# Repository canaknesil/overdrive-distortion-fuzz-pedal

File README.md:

# overdrive-distortion-fuzz-pedal
Overdrive, distortion, and fuzz with a single pedal

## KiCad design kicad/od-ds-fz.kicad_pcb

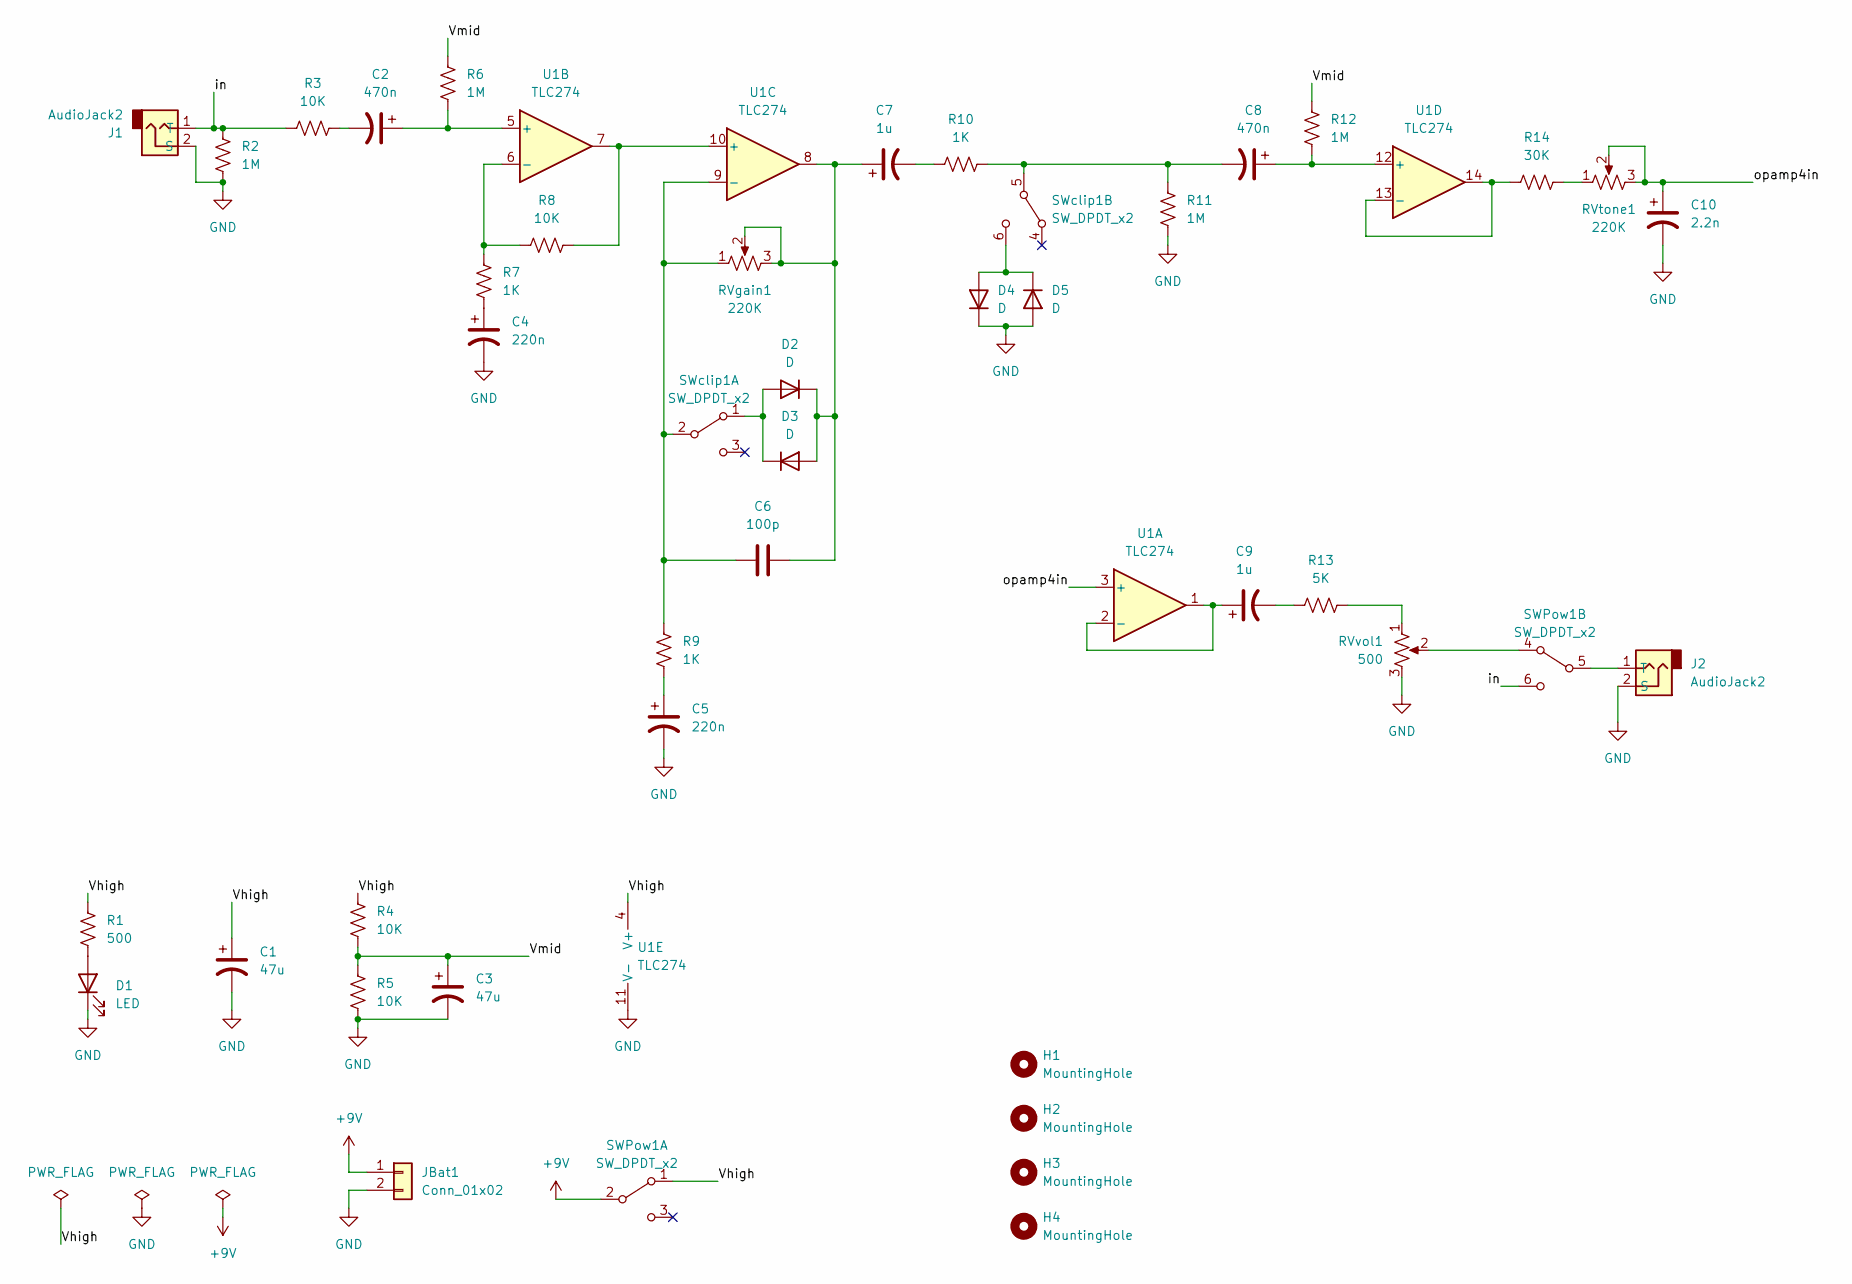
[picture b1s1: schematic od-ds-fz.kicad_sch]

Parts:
C1, C3: 47u; CP_Radial_D7.5mm_P2.50mm
C2, C8: 470n; CP_Radial_D7.5mm_P2.50mm
C4, C5: 220n; CP_Radial_D7.5mm_P2.50mm
C6: 100p; C_Disc_D5.1mm_W3.2mm_P5.00mm
C7, C9: 1u; CP_Radial_D7.5mm_P2.50mm
C10: 2.2n; C_Disc_D5.1mm_W3.2mm_P5.00mm
D1: LED; SolderWire-0.5sqmm_1x02_P4.6mm_D0.9mm_OD2.1mm
D2, D3, D4, D5: D; D_DO-15_P15.24mm_Horizontal
H1, H2, H3, H4: MountingHole; MountingHole_3.2mm_M3
J1, J2: AudioJack2; SolderWire-0.5sqmm_1x02_P4.6mm_D0.9mm_OD2.1mm
JBat1: Conn_01x02; SolderWire-0.5sqmm_1x02_P4.6mm_D0.9mm_OD2.1mm
R1: 500; R_Axial_DIN0207_L6.3mm_D2.5mm_P10.16mm_Horizontal
R2, R6, R11, R12: 1M; R_Axial_DIN0207_L6.3mm_D2.5mm_P10.16mm_Horizontal
R3, R4, R5, R8: 10K; R_Axial_DIN0207_L6.3mm_D2.5mm_P10.16mm_Horizontal
R7, R9, R10: 1K; R_Axial_DIN0207_L6.3mm_D2.5mm_P10.16mm_Horizontal
R13: 5K; R_Axial_DIN0207_L6.3mm_D2.5mm_P10.16mm_Horizontal
R14: 30K; R_Axial_DIN0207_L6.3mm_D2.5mm_P10.16mm_Horizontal
RVgain1: 220K; SolderWire-0.5sqmm_1x03_P4.6mm_D0.9mm_OD2.1mm
RVtone1: 220K; SolderWire-0.5sqmm_1x03_P4.6mm_D0.9mm_OD2.1mm
RVvol1: 500; SolderWire-0.5sqmm_1x03_P4.6mm_D0.9mm_OD2.1mm
SWPow1: SW_DPDT_x2; SolderWire-0.5sqmm_1x06_P4.6mm_D0.9mm_OD2.1mm
SWclip1: SW_DPDT_x2; SolderWire-0.5sqmm_1x06_P4.6mm_D0.9mm_OD2.1mm
U1: TLC274; DIP-14_W7.62mm

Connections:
+9V: JBat1.1, SWPow1.2 (B)
/Vhigh: C1.1, R1.1, R4.1, SWPow1.1 (A), U1.4 (V+)
/Vmid: C3.1, R4.2, R5.1, R6.1, R12.1
/in: J1.1 (T), R2.1, R3.1, SWPow1.6 (C)
/opamp4in: C10.1, RVtone1.2, RVtone1.3, U1.3 (+)
GND: C1.2, C3.2, C4.2, C5.2, C10.2, D1.1 (K), D4.1 (K), D5.2 (A), J1.2 (S), J2.2 (S), JBat1.2, R2.2, R5.2, R11.2, RVvol1.3, U1.11 (V-)
unnamed: C2.1, R6.2, U1.5 (+)
unnamed: C2.2, R3.2
unnamed: C4.1, R7.2
unnamed: C5.1, R9.2
unnamed: C6.1, R9.1, RVgain1.1, SWclip1.2 (B), U1.9 (-)
unnamed: C6.2, C7.1, D2.1 (K), D3.2 (A), RVgain1.2, RVgain1.3, U1.8
unnamed: C7.2, R10.1
unnamed: C8.1, R12.2, U1.12 (+)
unnamed: C8.2, R10.2, R11.1, SWclip1.5 (B)
unnamed: C9.1, U1.1, U1.2 (-)
unnamed: C9.2, R13.1
unnamed: D1.2 (A), R1.2
unnamed: D2.2 (A), D3.1 (K), SWclip1.1 (A)
unnamed: D4.2 (A), D5.1 (K), SWclip1.6 (C)
unnamed: R7.1, R8.1, U1.6 (-)
unnamed: R8.2, U1.7, U1.10 (+)
unnamed: R13.2, RVvol1.1
unnamed: R14.1, U1.13 (-), U1.14
unnamed: R14.2, RVtone1.1
unnamed: RVvol1.2, SWPow1.4 (A)
unnamed: J2.1 (T), SWPow1.5 (B)

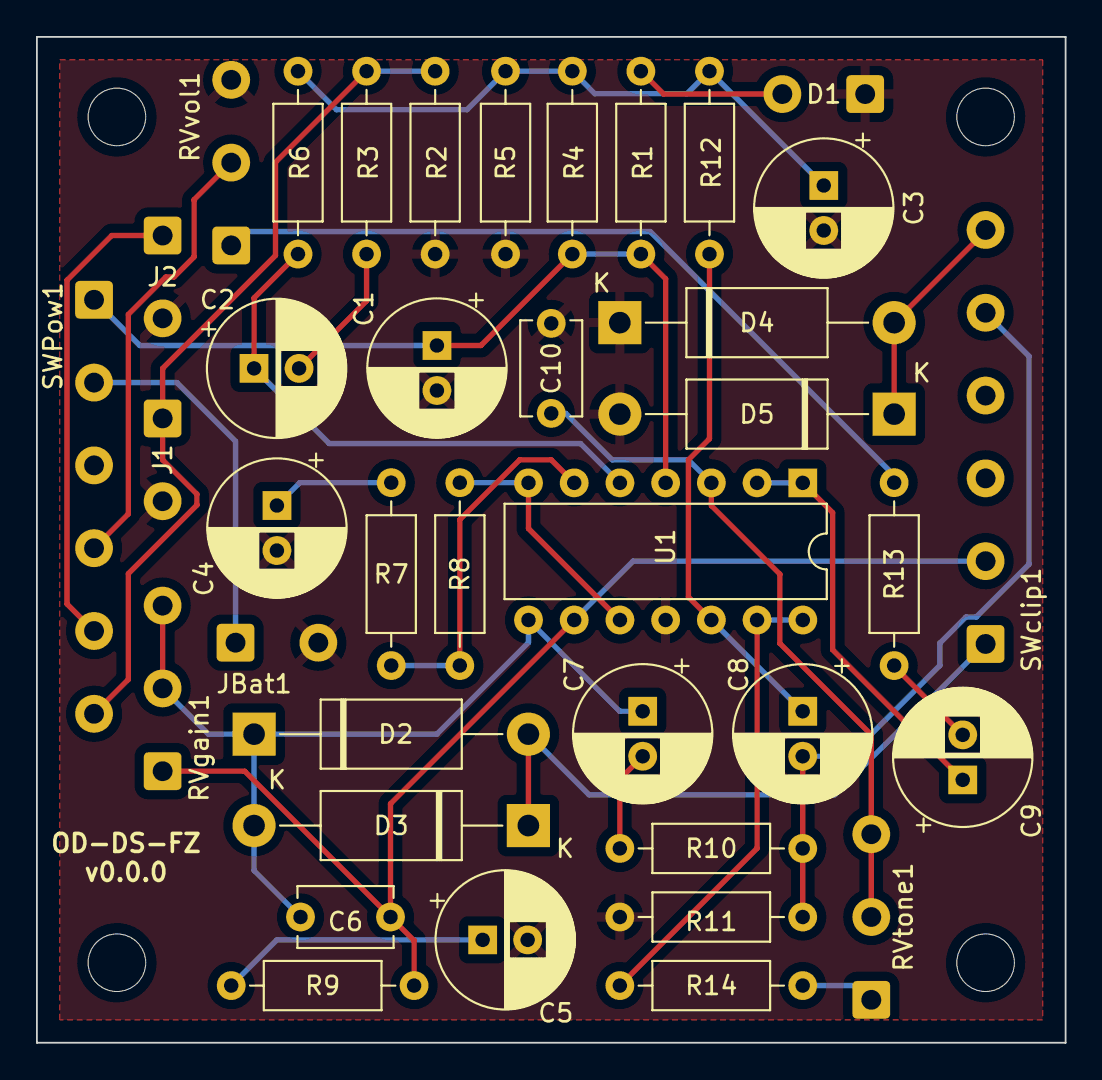
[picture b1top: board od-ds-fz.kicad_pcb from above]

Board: 2 copper layers, 57.1 x 55.9 mm, 42 parts (0 on the bottom side), 27 nets.

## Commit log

2022-09-26 Put completed livespice sch. Started kicad sch.
2022-10-11 finished sch, started footprint assignment
2022-10-11 Placed components on PCB.
2022-10-12 Placed mounting holes
2022-10-18 Precise placement
2022-10-18 routing and output files
